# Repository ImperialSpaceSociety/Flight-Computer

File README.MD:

# Imperial College Space Society - High-power Rocketry

## Rocket

The rocket was initially designed in a program called OpenRocket and then the particular components were designed in Fusion 360 and manufactured using 3D printers or a laser cutter.

## Flight computer

The flight computer is based on STM32 platform and the main diagram with its components can be seen below.

The following picture shows the 3D render of the flight computer designed in KiCAD.

## Receiver

The table documents the connection of the radio module into STM32 F446RE Nucleo Board used as a receiver.

| **Lambda 9D pin** | **STM32 Nucleo F446RE pin** |
|-------------------|-----------------------------|
| nSel - 16         |             GND             |
| SDI - 15          |             PA7             |
| SDO - 14          |             PA6             |
| SCLK - 13         |             PA5             |
| RESET - 12        |             PB12            |
| GND - 2           |             GND             |
| Vcc - 3           |             3V3             |
| RX_SWITCH - 4     |             PC2             |
| TX_SWITCH - 5     |             PA4             |

## Launch

The rocket was successfully launched and recovered on 9th July 2023 in Twycross, Leicestershire. The rocket reached the altitude of 721 m after 11.4 s of flight.

## Future improvements

- UART connection for debugging
- Button/jumper pin header for resetting STM32
- Code for IMU, magnetometer and flashchip
- FreeRTOS for the flight computer
- Modify serial logging script such that the incoming data is being processed and then saved as csv

## Repository content

- `Assets` - This folder contains images and plots for the `README.md` file.
- `Hardware/circuit board design v1.0` - First version of the hardware files of the flight computer.
- `Hardware/circuit board design v2.1` - Second version of the hardware files of the flight computer.
- `Hardware/Documentation` - Documentation files with spreadsheets containing components selection and power consumption.
- `Rocket` - This folder contains files simulation and design files for the rocket.
- `References` - This folder contains datasheets and manuals relevant to the components used for the flight computer.
- `Software/Dev board code` - This folder contains projects used to develop and test libraries for each of the components of the computer.
- `Software/revision_1` - First version of the flight computer software.
- `Software/revision_1_rx` - First version of the receiver software.
- `Software/serial_logging` - Code for the serial logging of the received data.

## Team (Academic year 2022/2023)

- Awais Khawaja (Rocket team lead)
- Rohan Kukreti, Stephen Liu (Nose cone)
- Heather Boatin (Recovery system)
- Denzel Goh, Dongxiao Jiang (Fins)
- Jack Crane (Engine mount)
- Timothy Newman, Lou Alsteens, Jakub Jędrzejewski (PCB)
- Václav Pavlíček, Richard Hu, Benny Liu (Software)

## Acknowledgements

We would like to thank Victor Boddy from the Electrical Engineering Undergraduate lab and the Advanced Hackspace staff for their help and support.

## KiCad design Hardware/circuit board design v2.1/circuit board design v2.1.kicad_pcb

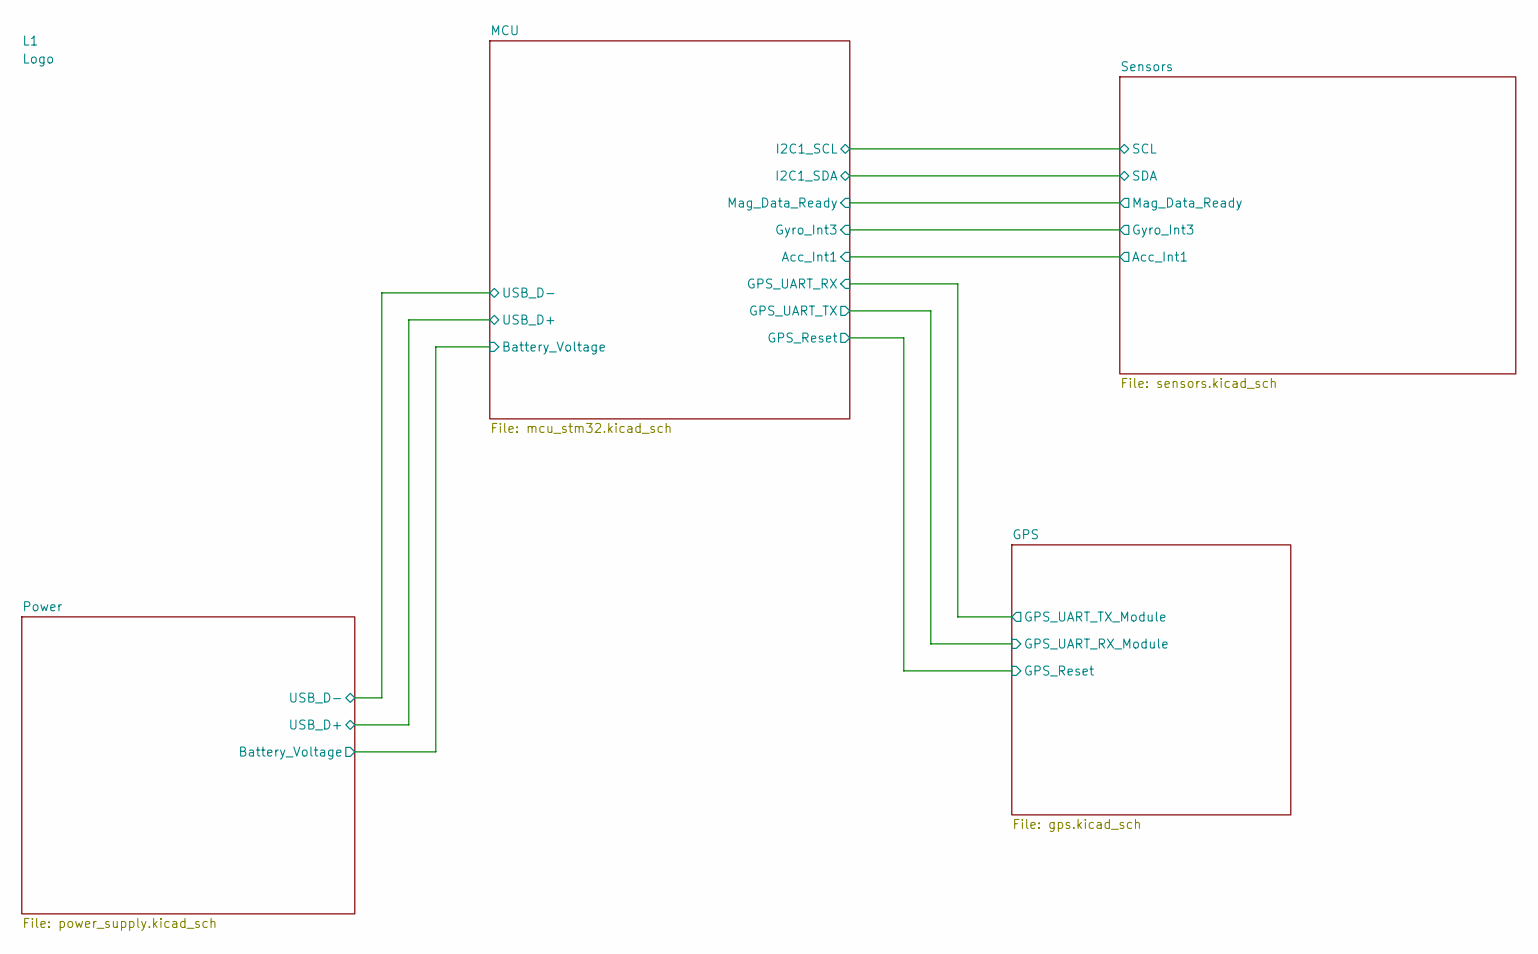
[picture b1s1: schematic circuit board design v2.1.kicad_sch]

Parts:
L1: Logo; ICSS_Logo

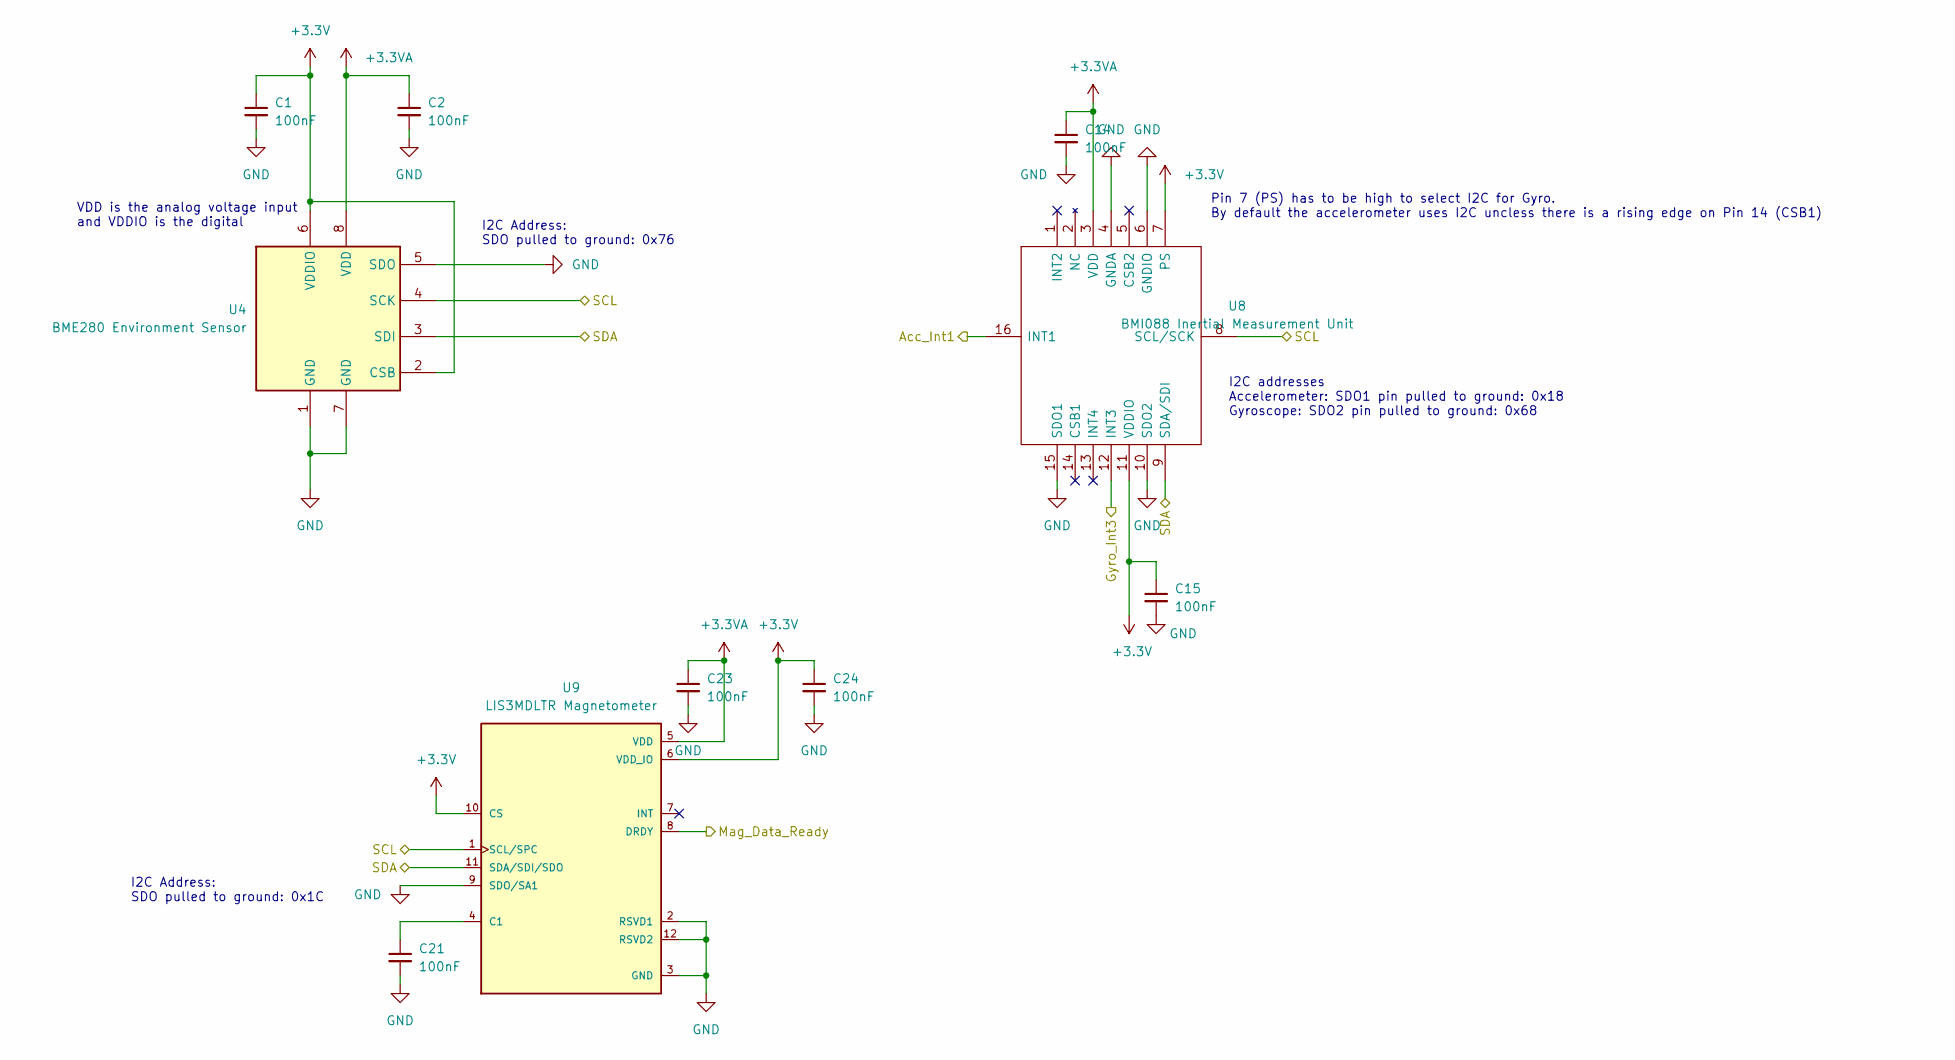
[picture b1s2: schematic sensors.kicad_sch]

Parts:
C1, C2, C14, C15, C21, C23, C24: 100nF; C_0603_1608Metric
U4: BME280 Environment Sensor; Bosch_LGA-8_2.5x2.5mm_P0.65mm_ClockwisePinNumbering
U8: BMI088 Inertial Measurement Unit; BMI088; Manufacturer_Part_Number BMI088; Mouser Part Number 262-BMI088
U9: LIS3MDLTR Magnetometer; XDCR_LIS3MDLTR; PARTREV 6

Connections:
+3.3V: C1.1, C15.1, C24.1, U4.2 (CSB), U4.6 (VDDIO), U8.7 (PS), U8.11 (VDDIO), U9.6 (VDD_IO), U9.10 (CS); also elsewhere on the board
+3.3VA: C2.1, C14.1, C23.1, U4.8 (VDD), U8.3 (VDD), U9.5 (VDD); also elsewhere on the board
/MCU/Acc_Int1: U8.16 (INT1); also elsewhere on the board
/MCU/Gyro_Int3: U8.12 (INT3); also elsewhere on the board
/MCU/I2C1_SCL: U4.4 (SCK), U8.8 (SCL/SCK), U9.1 (SCL/SPC); also elsewhere on the board
/MCU/I2C1_SDA: U4.3 (SDI), U8.9 (SDA/SDI), U9.11 (SDA/SDI/SDO); also elsewhere on the board
/MCU/Mag_Data_Ready: U9.8 (DRDY); also elsewhere on the board
GND: C1.2, C2.2, C14.2, C15.2, C21.2, C23.2, C24.2, U4.1 (GND), U4.5 (SDO), U4.7 (GND), U8.4 (GNDA), U8.6 (GNDIO), U8.10 (SDO2), U8.15 (SDO1), U9.2 (RSVD1), U9.3 (GND), U9.9 (SDO/SA1), U9.12 (RSVD2); also elsewhere on the board
unnamed: C21.1, U9.4 (C1)

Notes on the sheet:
VDD is the analog voltage input and VDDIO is the digital
Pin 7 (PS) has to be high to select I2C for Gyro. By default the accelerometer uses I2C uncless there is a rising edge on Pin 14 (CSB1)
I2C addresses Accelerometer: SDO1 pin pulled to ground: 0x18 Gyroscope: SDO2 pin pulled to ground: 0x68
I2C Address: SDO pulled to ground: 0x1C
I2C Address: SDO pulled to ground: 0x76

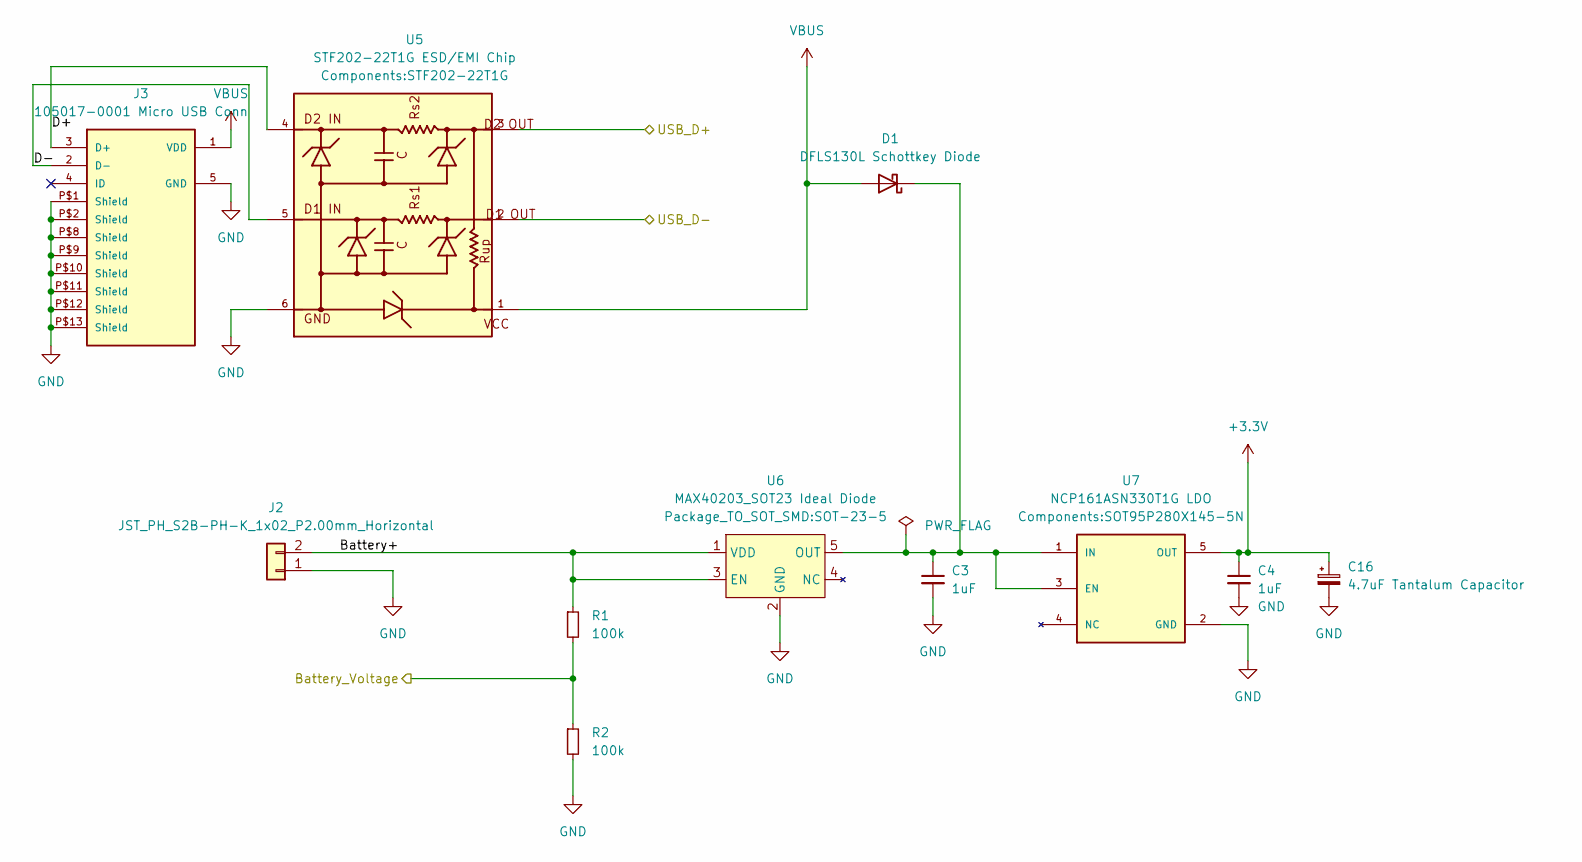
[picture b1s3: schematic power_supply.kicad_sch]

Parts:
C3, C4: 1uF; C_0603_1608Metric
C16: 4.7uF Tantalum Capacitor; C_1206_3216Metric_Pad1.33x1.80mm_HandSolder
D1: DFLS130L Schottkey Diode; PowerDI123
J2: JST_PH_S2B-PH-K_1x02_P2.00mm_Horizontal
J3: 105017-0001 Micro USB Conn; MOLEX_105017-0001
R1, R2: 100k; R_0603_1608Metric
U5: STF202-22T1G ESD/EMI Chip; STF202-22T1G
U6: MAX40203_SOT23 Ideal Diode; SOT-23-5
U7: NCP161ASN330T1G LDO; SOT95P280X145-5N; PARTREV Rev. 18

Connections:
+3.3V: C4.1, C16.1, U7.5 (OUT); also elsewhere on the board
/MCU/Battery_Voltage: R1.2, R2.1; also elsewhere on the board
/MCU/USB_D+: U5.3; also elsewhere on the board
/MCU/USB_D-: U5.2; also elsewhere on the board
/Power/Battery+: J2.2, R1.1, U6.1 (VDD), U6.3 (EN)
/Power/D+: J3.3 (D+), U5.4
/Power/D-: J3.2 (D-), U5.5
GND: C3.2, C4.2, C16.2, J2.1, J3.5 (GND), J3.P$1 (Shield), J3.P$2 (Shield), J3.P$8 (Shield), J3.P$9 (Shield), J3.P$10 (Shield), J3.P$11 (Shield), J3.P$12 (Shield), J3.P$13 (Shield), R2.2, U5.6, U6.2 (GND), U7.2 (GND); also elsewhere on the board
unnamed: C3.1, D1.1 (K), U6.5 (OUT), U7.1 (IN), U7.3 (EN)
VBUS: D1.2 (A), J3.1 (VDD), U5.1

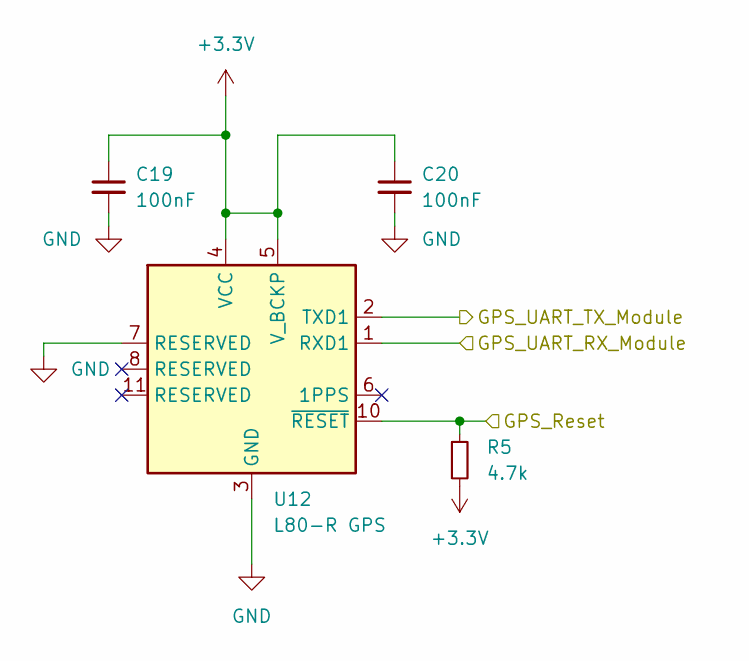
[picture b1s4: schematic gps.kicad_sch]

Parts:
C19, C20: 100nF; C_0603_1608Metric
R5: 4.7k; R_0603_1608Metric
U12: L80-R GPS; Quectel_L80-R

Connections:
+3.3V: C19.1, C20.1, R5.2, U12.4 (VCC), U12.5 (V_BCKP); also elsewhere on the board
/GPS/GPS_Reset: R5.1, U12.10 (~RESET); also elsewhere on the board
/GPS/GPS_UART_RX_Module: U12.1 (RXD1); also elsewhere on the board
/GPS/GPS_UART_TX_Module: U12.2 (TXD1); also elsewhere on the board
GND: C19.2, C20.2, U12.3 (GND), U12.7 (RESERVED), U12.12 (GND); also elsewhere on the board

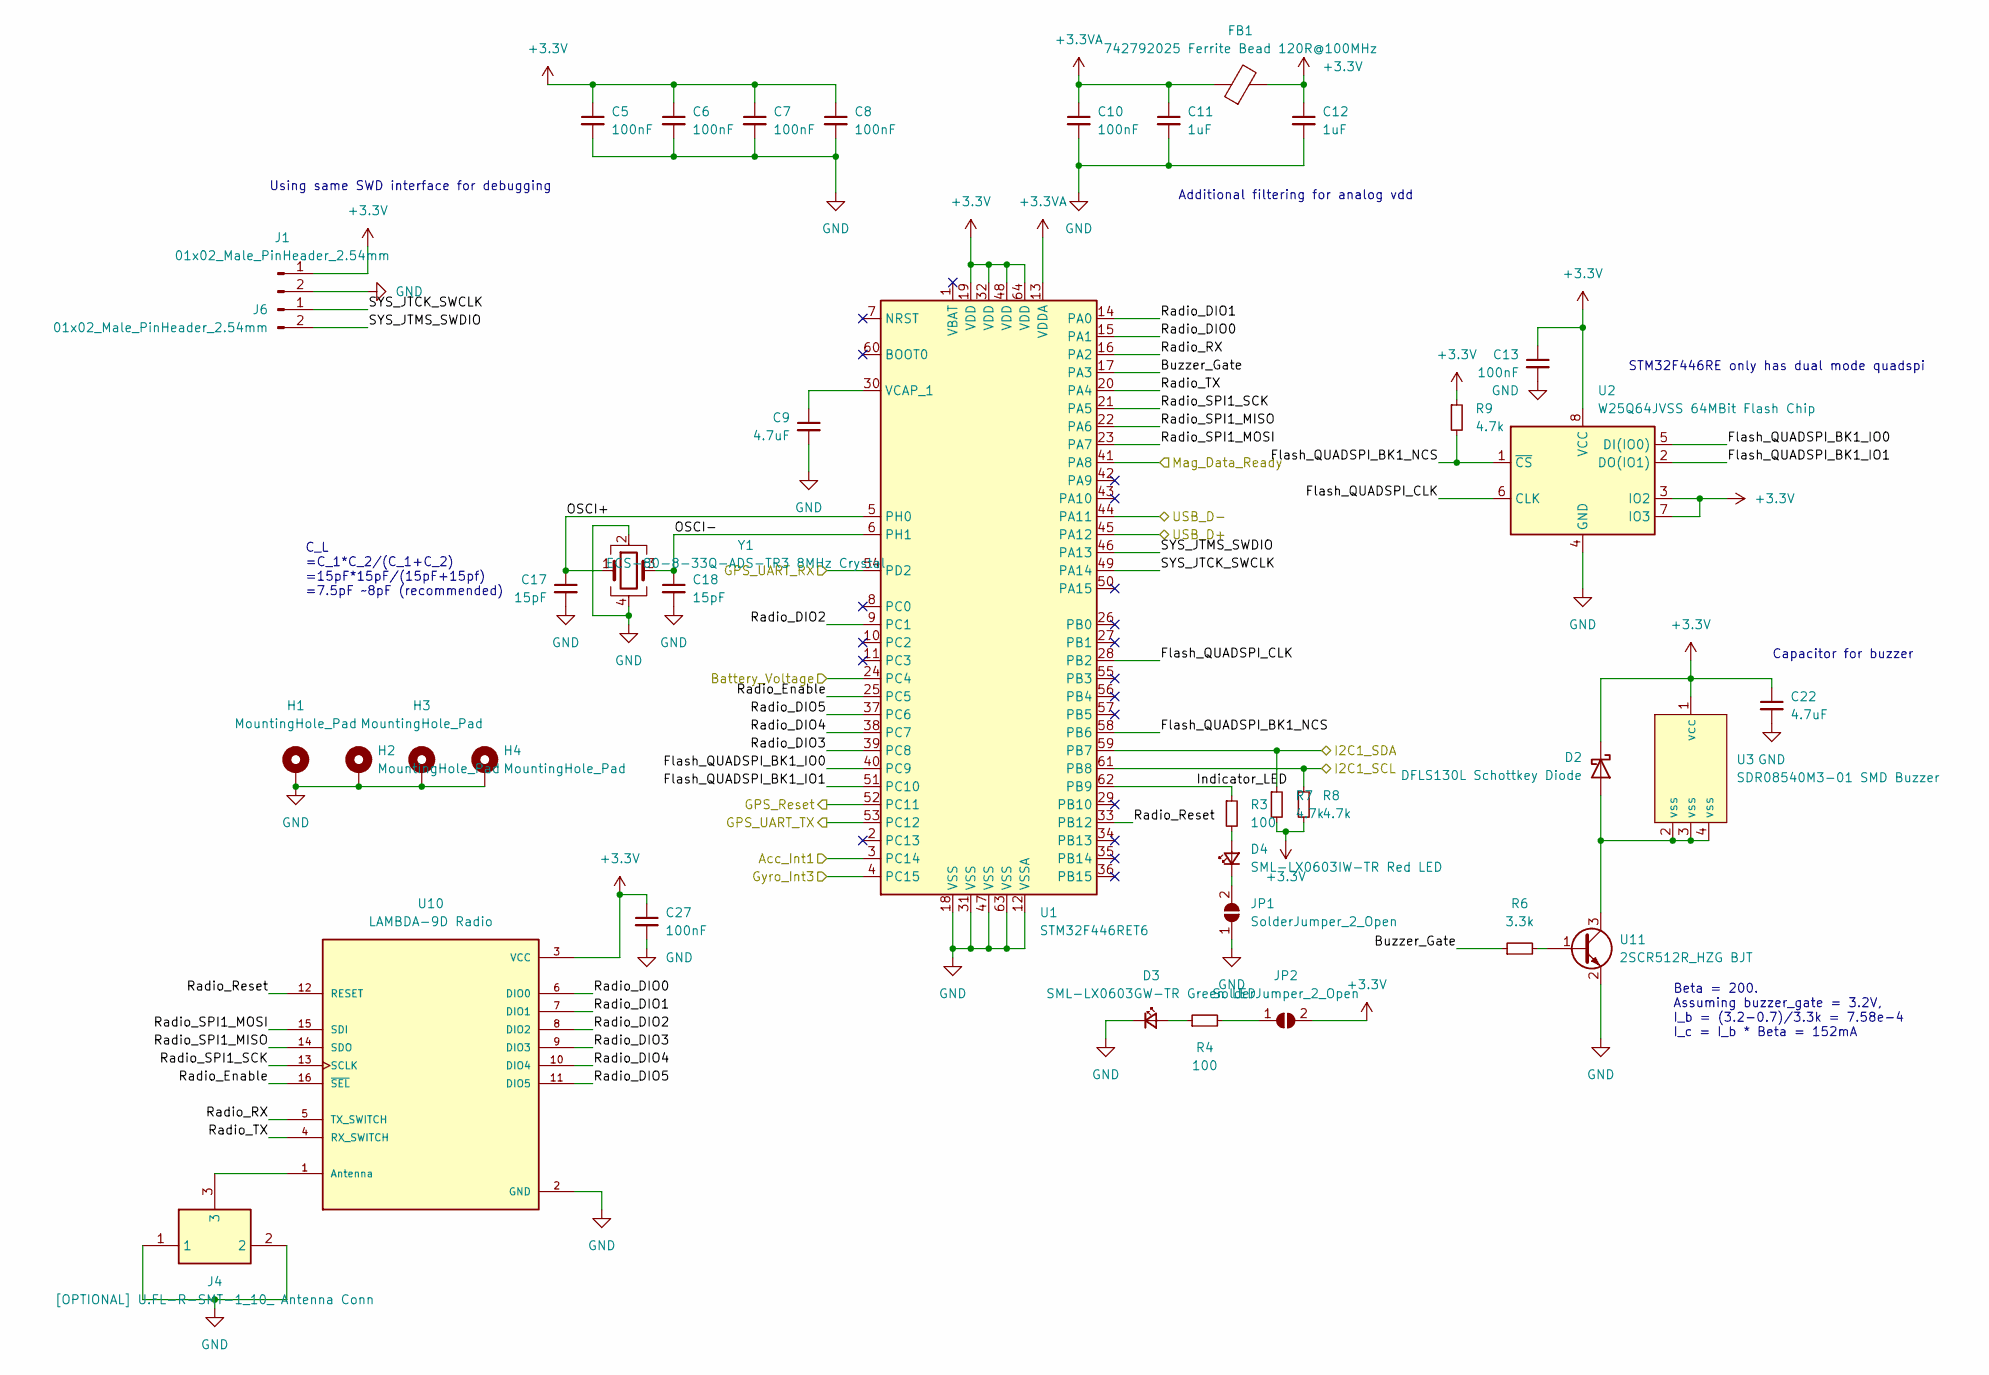
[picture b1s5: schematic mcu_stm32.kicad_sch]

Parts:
C5, C6, C7, C8, C10, C13: 100nF; C_0603_1608Metric
C9, C22: 4.7uF; C_0603_1608Metric
C11, C12: 1uF; C_0603_1608Metric
C17, C18: 15pF; C_0603_1608Metric
C27: 100nF; C_0603_1608Metric_Pad1.08x0.95mm_HandSolder
D2: DFLS130L Schottkey Diode; PowerDI123
D3: SML-LX0603GW-TR Green LED; C_0603_1608Metric
D4: SML-LX0603IW-TR Red LED; C_0603_1608Metric
FB1: 742792025 Ferrite Bead 120R@100MHz; R_0805_2012Metric_Pad1.20x1.40mm_HandSolder
H1, H2, H3, H4: MountingHole_Pad; MountingHole_3.2mm_M3_ISO7380_Pad_TopBottom
J1, J6: 01x02_Male_PinHeader_2.54mm; PinHeader_1x02_P2.54mm_Vertical
J4: [OPTIONAL] U.FL-R-SMT-1_10_ Antenna Conn; U.FL-R-SMT-1_10_; Manufacturer_Part_Number U.FL-R-SMT-1(10); Mouser Part Number 798-U.FL-R-SMT-110
JP1, JP2: SolderJumper_2_Open; SolderJumper-2_P1.3mm_Open_TrianglePad1.0x1.5mm
R3, R4: 100; R_0603_1608Metric
R6: 3.3k; R_0603_1608Metric
R7, R8, R9: 4.7k; R_0603_1608Metric
U1: STM32F446RET6; LQFP-64_10x10mm_P0.5mm
U2: W25Q64JVSS 64MBit Flash Chip; W25Q64JVSSIQ
U3: SDR08540M3-01 SMD Buzzer; SDR08540M3-01 Buzzer
U10: LAMBDA-9D Radio; XCVR_LAMBDA-9D; PARTREV N/A
U11: 2SCR512R_HZG BJT; 2SCR512RHZG
Y1: ECS-80-8-33Q-ADS-TR3 8MHz Crystal; ECS-80-8-33Q-ADS-TR3 Crystal

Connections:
+3.3V: C5.1, C6.1, C7.1, C8.1, C12.1, C13.1, C22.1, C27.1, D2.1 (K), FB1.2, J1.1, JP2.2 (B), R7.2, R8.2, R9.1, U1.19 (VDD), U1.32 (VDD), U1.48 (VDD), U1.64 (VDD), U2.3 (IO2), U2.7 (IO3), U2.8 (VCC), U3.1 (vcc), U10.3 (VCC); also elsewhere on the board
+3.3VA: C10.1, C11.1, FB1.1, U1.13 (VDDA); also elsewhere on the board
/GPS/GPS_Reset: U1.52 (PC11); also elsewhere on the board
/GPS/GPS_UART_RX_Module: U1.53 (PC12); also elsewhere on the board
/GPS/GPS_UART_TX_Module: U1.54 (PD2); also elsewhere on the board
/MCU/Acc_Int1: U1.3 (PC14); also elsewhere on the board
/MCU/Battery_Voltage: U1.24 (PC4); also elsewhere on the board
/MCU/Buzzer_Gate: R6.1, U1.17 (PA3)
/MCU/Flash_QUADSPI_BK1_IO0: U1.40 (PC9), U2.5 (DI(IO0))
/MCU/Flash_QUADSPI_BK1_IO1: U1.51 (PC10), U2.2 (DO(IO1))
/MCU/Flash_QUADSPI_BK1_NCS: R9.2, U1.58 (PB6), U2.1 (~CS)
/MCU/Flash_QUADSPI_CLK: U1.28 (PB2), U2.6 (CLK)
/MCU/Gyro_Int3: U1.4 (PC15); also elsewhere on the board
/MCU/I2C1_SCL: R8.1, U1.61 (PB8); also elsewhere on the board
/MCU/I2C1_SDA: R7.1, U1.59 (PB7); also elsewhere on the board
/MCU/Indicator_LED: R3.1, U1.62 (PB9)
/MCU/Mag_Data_Ready: U1.41 (PA8); also elsewhere on the board
/MCU/OSCI+: C17.1, U1.5 (PH0), Y1.1
/MCU/OSCI-: C18.1, U1.6 (PH1), Y1.3
/MCU/Radio_DIO0: U1.15 (PA1), U10.6 (DIO0)
/MCU/Radio_DIO1: U1.14 (PA0), U10.7 (DIO1)
/MCU/Radio_DIO2: U1.9 (PC1), U10.8 (DIO2)
/MCU/Radio_DIO3: U1.39 (PC8), U10.9 (DIO3)
/MCU/Radio_DIO4: U1.38 (PC7), U10.10 (DIO4)
/MCU/Radio_DIO5: U1.37 (PC6), U10.11 (DIO5)
/MCU/Radio_Enable: U1.25 (PC5), U10.16 (~SEL)
/MCU/Radio_RX: U1.16 (PA2), U10.5 (TX_SWITCH)
/MCU/Radio_Reset: U1.33 (PB12), U10.12 (RESET)
/MCU/Radio_SPI1_MISO: U1.22 (PA6), U10.14 (SDO)
/MCU/Radio_SPI1_MOSI: U1.23 (PA7), U10.15 (SDI)
/MCU/Radio_SPI1_SCK: U1.21 (PA5), U10.13 (SCLK)
/MCU/Radio_TX: U1.20 (PA4), U10.4 (RX_SWITCH)
/MCU/SYS_JTCK_SWCLK: J6.1, U1.49 (PA14)
/MCU/SYS_JTMS_SWDIO: J6.2, U1.46 (PA13)
/MCU/USB_D+: U1.45 (PA12); also elsewhere on the board
/MCU/USB_D-: U1.44 (PA11); also elsewhere on the board
GND: C5.2, C6.2, C7.2, C8.2, C9.2, C10.2, C11.2, C12.2, C13.2, C17.2, C18.2, C22.2, C27.2, D3.1 (K), H1.1, H2.1, H3.1, H4.1, J1.2, J4.1, J4.2, JP1.1 (A), U1.12 (VSSA), U1.18 (VSS), U1.31 (VSS), U1.47 (VSS), U1.63 (VSS), U2.4 (GND), U10.2 (GND), U11.2 (E), Y1.2, Y1.4; also elsewhere on the board
unnamed: C9.1, U1.30 (VCAP_1)
unnamed: D2.2 (A), U3.2 (vss), U3.3 (vss), U3.4 (vss), U11.3 (C)
unnamed: D3.2 (A), R4.1
unnamed: D4.1 (K), JP1.2 (B)
unnamed: D4.2 (A), R3.2
unnamed: J4.3, U10.1 (Antenna)
unnamed: JP2.1 (A), R4.2
unnamed: R6.2, U11.1 (B)

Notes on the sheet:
Capacitor for buzzer
Using same SWD interface for debugging
STM32F446RE only has dual mode quadspi
Additional filtering for analog vdd
C_L =C_1*C_2/(C_1+C_2) =15pF*15pF/(15pF+15pf) =7.5pF ~8pF (recommended)
Beta = 200. Assuming buzzer_gate = 3.2V, I_b = (3.2-0.7)/3.3k = 7.58e-4 I_c = I_b * Beta = 152mA

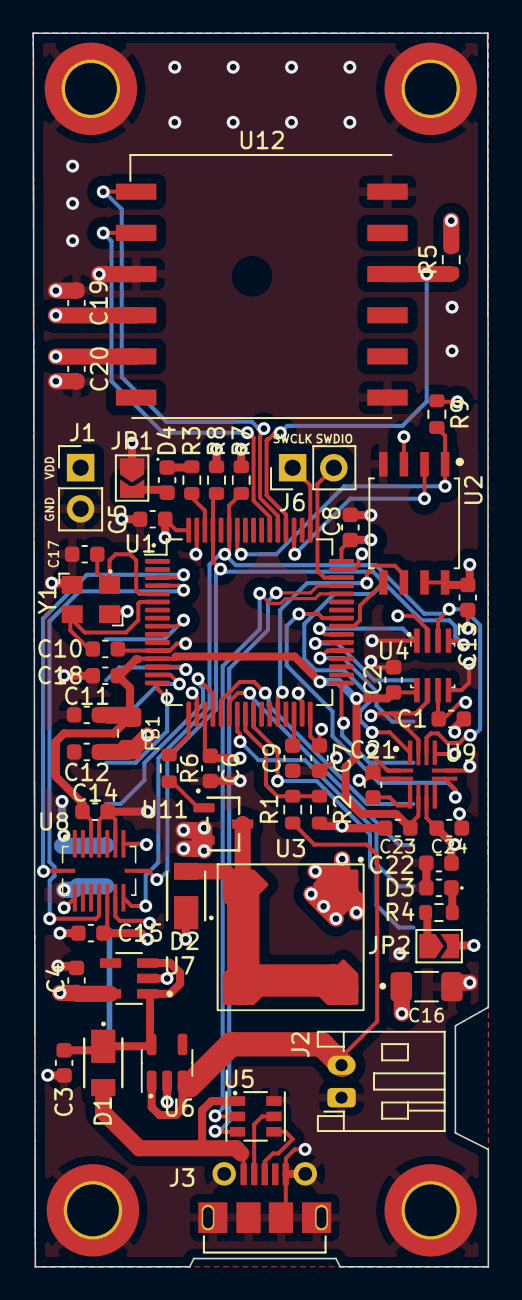
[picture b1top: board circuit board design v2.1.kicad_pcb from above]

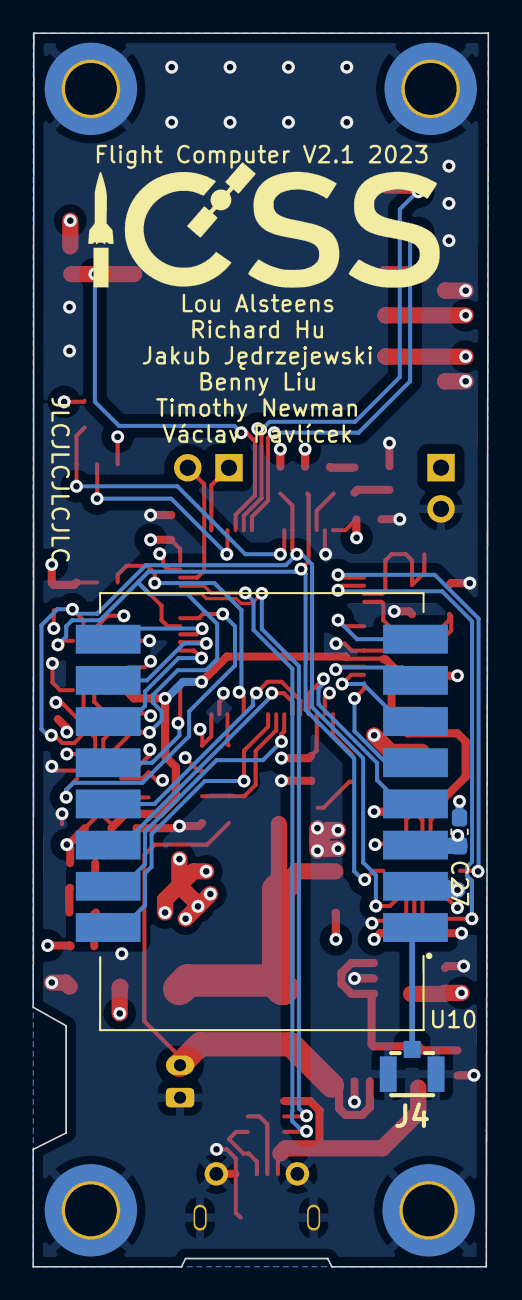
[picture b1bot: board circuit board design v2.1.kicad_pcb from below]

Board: 4 copper layers, 28.1 x 76.1 mm, 64 parts (4 on the bottom side), 51 nets.

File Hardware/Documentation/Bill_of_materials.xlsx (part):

Source: | C:\Users\timot\Documents\Programming\SpaceSoc\Flight-Computer\Hardware\circuit 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
Date: | 45080.649074074077
Tool: | Eeschema (6.0.8)
Generator: | C:\Program Files\KiCad\6.0\bin\scripting\plugins/bom_csv_grouped_by_value.py
Component Count: | 56
Individual Components:
Item | Qty | Reference(s) | Value | LibPart | Footprint | Datasheet | AVAILABILITY | Arrow Part Number | Arrow Price/Stock | DESCRIPTION | Datasheet_1 | Description | Footprint_1 | Height | MANUFACTURER | MAXIMUM_PACKAGE_HEIGHT | MF | MP | Manufacturer_Name | Manufacturer_Part_Number | Mouser Part Number | Mouser Price/Stock | PACKAGE | PARTREV | PRICE | Reference_1 | SNAPEDA_PACKAGE_ID | SNAPEDA_PN | STANDARD | Value_1
 |  | C1 | 100nF | Components:C_0603 | Components:C_0603_1608Metric | ~
 |  | C2 | 100nF | Components:C_0603 | Components:C_0603_1608Metric | ~
 |  | C3 | 1uF | Components:C_0603 | Components:C_0603_1608Metric | ~
 |  | C4 | 1uF | Components:C_0603 | Components:C_0603_1608Metric | ~
 |  | C5 | 100nF | Components:C_0603 | Components:C_0603_1608Metric | ~
 |  | C6 | 100nF | Components:C_0603 | Components:C_0603_1608Metric | ~
 |  | C7 | 100nF | Components:C_0603 | Components:C_0603_1608Metric | ~
 |  | C8 | 100nF | Components:C_0603 | Components:C_0603_1608Metric | ~
 |  | C9 | 4.7uF | Components:C_0603 | Components:C_0603_1608Metric | ~
 |  | C10 | 100nF | Components:C_0603 | Components:C_0603_1608Metric | ~
 |  | C11 | 1uF | Components:C_0603 | Components:C_0603_1608Metric | ~
 |  | C12 | 1uF | Components:C_0603 | Components:C_0603_1608Metric | ~
 |  | C13 | 100nF | Components:C_0603 | Components:C_0603_1608Metric | ~
 |  | C14 | 100nF | Components:C_0603 | Components:C_0603_1608Metric | ~
 |  | C15 | 100nF | Components:C_0603 | Components:C_0603_1608Metric | ~
 |  | C16 | 4.7uF Tantalum Capacitor | Device:C_Polarized_Small | Capacitor_SMD:C_1206_3216Metric_Pad1.33x1.80mm_HandSolder | ~
 |  | C17 | 15pF | Components:C_0603 | Components:C_0603_1608Metric | ~
 |  | C18 | 15pF | Components:C_0603 | Components:C_0603_1608Metric | ~
 |  | C19 | 100nF | Components:C_0603 | Components:C_0603_1608Metric | ~
 |  | C20 | 100nF | Components:C_0603 | Components:C_0603_1608Metric | ~
 |  | C21 | 100nF | Components:C_0603 | Components:C_0603_1608Metric | ~
 |  | C22 | 4.7uF | Components:C_0603 | Components:C_0603_1608Metric | ~
 |  | C23 | 100nF | Components:C_0603 | Components:C_0603_1608Metric | ~
 |  | C24 | 100nF | Components:C_0603 | Components:C_0603_1608Metric | ~
 |  | C27 | 100nF | Device:C_Small | Capacitor_SMD:C_0603_1608Metric_Pad1.08x0.95mm_HandSolder | ~
 |  | D1 | DFLS130L Schottkey Diode | Components:DFLS130L | Components:PowerDI123 | ~
 |  | D2 | DFLS130L Schottkey Diode | Components:DFLS130L | Components:PowerDI123 | ~
 |  | D3 | SML-LX0603GW-TR Green LED | Components:LED_0603 | Components:C_0603_1608Metric | ~
 |  | D4 | SML-LX0603IW-TR Red LED | Components:LED_0603 | Components:C_0603_1608Metric | ~
 |  | FB1 | 742792025 Ferrite Bead 120R@100MHz | Device:FerriteBead | Resistor_SMD:R_0805_2012Metric_Pad1.20x1.40mm_HandSolder | ~
 |  | J1 | 01x02_Male_PinHeader_2.54mm | Connector:Conn_01x02_Male | Connector_PinHeader_2.54mm:PinHeader_1x02_P2.54mm_Vertical | ~
 |  | J2 | JST_PH_S2B-PH-K_1x02_P2.00mm_Horizontal | Connector_Generic:Conn_01x02 | Components:JST_PH_S2B-PH-K_1x02_P2.00mm_Horizontal | ~
 |  | J3 | 105017-0001 Micro USB Conn | Components:105017-0001 | MOLEX_105017-0001 | https://www.mouser.co.uk/datasheet/2/276/1/1050170001_IO_CON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
 |  | J4 | [OPTIONAL] U.FL-R-SMT-1_10_ Antenna Conn | Components:U.FL-R-SMT-1_10_ | Components:U.FL-R-SMT-1_10_ | https://www.hirose.com/product/document?clcode=CL0331-0472-2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 |  | U.FL-R-SMT-1(10) | https://www.arrow.com/en/products/u.fl-r-smt-1-10/hirose-electric |  | https://www.hirose.com/product/document?clcode=CL0331-0472-2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 |  | U.FL-R-SMT-1(10) |  |  |  |  |  | Hirose | U.FL-R-SMT-1(10) | 798-U.FL-R-SMT-110 | https://www.mouser.co.uk/ProductDetail/Hirose-Connector/U.FL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 |  |  |  | J |  |  |  | U.FL-R-SMT-1_10_
 |  | J6 | 01x02_Male_PinHeader_2.54mm | Connector:Conn_01x02_Male | Connector_PinHeader_2.54mm:PinHeader_1x02_P2.54mm_Vertical | ~
 |  | R1 | 100k | Components:R_0603 | Components:R_0603_1608Metric | ~
 |  | R2 | 100k | Components:R_0603 | Components:R_0603_1608Metric | ~
 |  | R3 | 100 | Components:R_0603 | Components:R_0603_1608Metric | ~
 |  | R4 | 100 | Components:R_0603 | Components:R_0603_1608Metric | ~
 |  | R5 | 4.7k | Components:R_0603 | Components:R_0603_1608Metric | ~
 |  | R6 | 3.3k | Components:R_0603 | Components:R_0603_1608Metric | ~
 |  | R7 | 4.7k | Components:R_0603 | Components:R_0603_1608Metric | ~
 |  | R8 | 4.7k | Components:R_0603 | Components:R_0603_1608Metric | ~
 |  | U1 | STM32F446RETx | MCU_ST_STM32F4:STM32F446RETx | Components:LQFP-64_10x10mm_P0.5mm | http://www.st.com/st-web-ui/static/active/en/resource/techni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
 |  | U2 | W25Q64JVSS 64MBit Flash Chip | Components:W25Q64JVSS | Components:W25Q64JVSSIQ | https://www.winbond.com/resource-files/W25Q64JV%20RevK%20031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
 |  | U3 | SDR08540M3-01 SMD Buzzer | Components:SDR08540M3-01 | Components:SDR08540M3-01 Buzzer | https://docs.rs-online.com/16ce/0900766b815934ae.pdf
 |  | U4 | BME280 Environment Sensor | Sensor:BME280 | Package_LGA:Bosch_LGA-8_2.5x2.5mm_P0.65mm_ClockwisePinNumbering | https://ae-bst.resource.bosch.com/media/_tech/media/datashee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
 |  | U5 | STF202-22T1G ESD/EMI Chip | Components:STF202-22T1G | Components:STF202-22T1G
 |  | U6 | MAX40203_SOT23 Ideal Diode | Components:MAX40203_SOT23 | Package_TO_SOT_SMD:SOT-23-5
 |  | U7 | NCP161ASN330T1G LDO | Components:NCP161ASN180T1G | Components:SOT95P280X145-5N | https://www.mouser.co.uk/datasheet/2/308/1/NCP161_D-2316989.pdf |  |  |  |  |  |  |  |  | Onsemi | 1.45 mm |  |  |  |  |  |  |  | Rev. 18 |  |  |  | NCP161ASN180T1G | IPC-7351B
 |  | U8 | BMI088 Inertial Measurement Unit | Components:BMI088 | Components:BMI088 | https://datasheet.datasheetarchive.com/originals/distributor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 |  | BMI088 | https://www.arrow.com/en/products/bmi088/bosch?region=europe |  |  | Inertial Measurement Unit Digital Output 2.5V/3.3V Automotive |  | 1.45 |  |  |  |  | BOSCH | BMI088 | 262-BMI088 | https://www.mouser.co.uk/ProductDetail/Bosch-Sensortec/BMI08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
 |  | U9 | LIS3MDLTR Magnetometer | Components:LIS3MDLTR | Components:XDCR_LIS3MDLTR |  | Unavailable |  |  | LIS3MDL Series 3 Axis Â±2/Â±8/Â±12/Â±16 g 3.6V High Performance Magnetometer LG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 |  |  |  |  |  | 1mm | STMicroelectronics | LIS3MDLTR |  |  |  |  | VFLGA-12 STMicroelectronics | 6 | None |  |  |  | Manufacturer Recommendation
 |  | U10 | LAMBDA-9D Radio | Components:LAMBDA-9D | Components:XCVR_LAMBDA-9D |  |  |  |  |  |  |  |  |  | RF Solutions | 5.81 mm |  |  |  |  |  |  |  | N/A |  |  | 63698 | LAMBDA-9D | Manufacturer Recommendations
 |  | U11 | 2SCR512R_HZG BJT | Components:2SCR512R_HZG | Components:2SCR512RHZG | https://fscdn.rohm.com/en/products/databook/datasheet/discre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
 |  | U12 | L80-R GPS | Components:L80-R | Components:Quectel_L80-R | https://www.quectel.com/UploadImage/Downlad/Quectel_L80-R_Ha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
 |  | Y1 | ECS-80-8-33Q-ADS-TR3 8MHz Crystal | Device:Crystal_GND24 | Components:ECS-80-8-33Q-ADS-TR3 Crystal | ~
Collated Components:
Item | Qty | Reference(s) | Value |  |  |  |  |  |  |  |  |  |  |  |  |  |  |  |  |  |  |  |  |  |  |  |  |  | STANDARD | Value_1
1 | 15 | C1, C2, C5, C6, C7, C8, C10, C13, C14, C15, C19, C20, C21, C23, C24 | 100nF
2 | 4 | C3, C4, C11, C12 | 1uF
3 | 2 | C9, C22 | 4.7uF
4 | 1 | C16 | 4.7uF Tantalum Capacitor
5 | 2 | C17, C18 | 15pF
6 | 1 | C27 | 100nF
7 | 2 | D1, D2 | DFLS130L Schottkey Diode
8 | 1 | D3 | SML-LX0603GW-TR Green LED
9 | 1 | D4 | SML-LX0603IW-TR Red LED
10 | 1 | FB1 | 742792025 Ferrite Bead 120R@100MHz
11 | 2 | J1, J6 | 01x02_Male_PinHeader_2.54mm
12 | 1 | J2 | JST_PH_S2B-PH-K_1x02_P2.00mm_Horizontal
13 | 1 | J3 | 105017-0001 Micro USB Conn
14 | 1 | J4 | [OPTIONAL] U.FL-R-SMT-1_10_ Antenna Conn
15 | 2 | R1, R2 | 100k
16 | 2 | R3, R4 | 100
17 | 3 | R5, R7, R8 | 4.7k
18 | 1 | R6 | 3.3k
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
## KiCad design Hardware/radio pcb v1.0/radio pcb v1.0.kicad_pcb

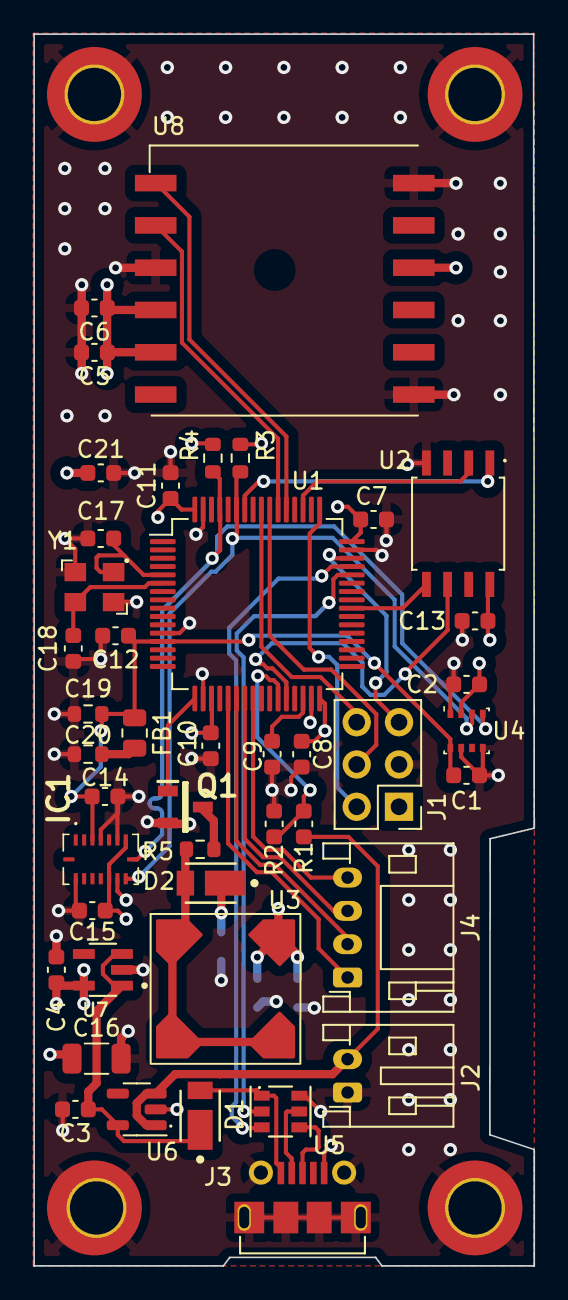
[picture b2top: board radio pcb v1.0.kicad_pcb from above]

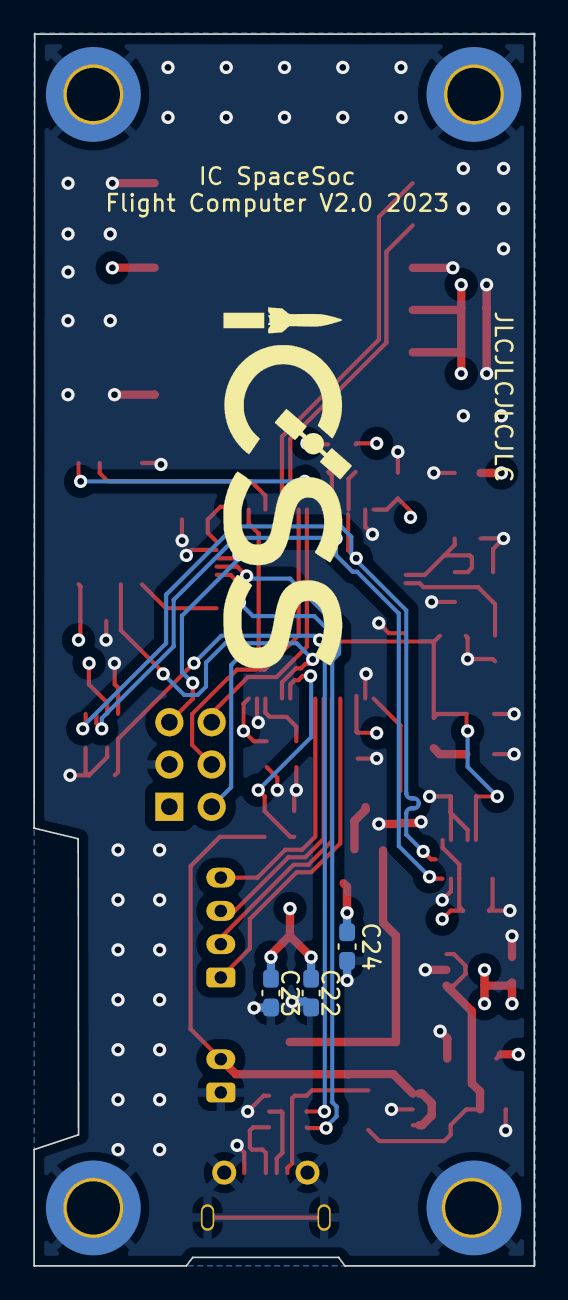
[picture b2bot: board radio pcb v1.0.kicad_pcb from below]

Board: 4 copper layers, 30.0 x 74.0 mm, 51 parts (3 on the bottom side), 34 nets.

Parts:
C1, C2, C5, C6, C7, C8, C10, C11, C12, C13, C14, C15: 100nF; C_0603_1608Metric
C3, C4: 1uF; C_0603_1608Metric
C9: 4.7u; C_0603_1608Metric
C16: 1uF; C_1206_3216Metric
C17, C18: 8pF; C_0603_1608Metric
C19, C20: 1uF; R_0603_1608Metric
C21: 4.7uF; C_0603_1608Metric
C22, C23, C24: 1uF; C_0603_1608Metric_Pad1.08x0.95mm_HandSolder
D1, D2: DFLS130L; PowerDI123
FB1: 120R@100MHz; R_0805_2012Metric
H1, H2, H3, H4: MountingHole_Pad; MountingHole_3.2mm_M3_ISO7380_Pad_TopBottom
IC1: BMI088
J1: Conn_01x06_Male; PinHeader_2x03_P2.54mm_Vertical
J2: Conn_01x02; JST_PH_S2B-PH-K_1x02_P2.00mm_Horizontal
J3: 105017-0001; MOLEX_105017-0001
J4: Conn_01x04; JST_PH_S4B-PH-K_1x04_P2.00mm_Horizontal
Q1: 2N7002-7-F; SOT96P240X120-3N
R1, R2: 100k; C_0603_1608Metric
R3, R4: 4.7k; R_0603_1608Metric
R5: 68; R_0603_1608Metric
U1: STM32F446RETx; LQFP-64_10x10mm_P0.5mm
U2: W25Q64JVSS; W25Q64JVSSIQ
U3: SDR08540M3-01; SDR08540M3-01 Buzzer
U4: BME280; Bosch_LGA-8_2.5x2.5mm_P0.65mm_ClockwisePinNumbering
U5: STF202-22T1G
U6: MAX40203_SOT23; SOT-23-5
U7: NCP161ASN330T1G; SOT95P280X145-5N
U8: L80-M39; Quectel_L80-R
Y1: Crystal_GND24; ECS-80-8-33Q-ADS-TR3 Crystal

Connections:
+3.3V: C2.1, C4.1, C5.1, C6.1, C7.1, C8.1, C10.1, C11.1, C13.1, C15.2, C16.1, C21.1, C22.1, C23.1, C24.1, D2.1 (K), IC1.7 (PS), IC1.11 (VDDIO), J1.1, R3.2, R4.2, U1.19 (VDD), U1.32 (VDD), U1.48 (VDD), U1.64 (VDD), U2.8 (VCC), U3.1 (vcc), U4.2 (CSB), U7.5 (OUT), U8.4 (VCC), U8.5 (V_BCKP), U8.10 (~RESET)
+3.3VA: C1.1, C12.1, C14.1, C19.1, FB1.1, IC1.3 (VDD), U1.13 (VDDA), U4.8 (VDD)
/GPS/rx_gps: U1.53 (PC12), U8.1 (RXD1)
/GPS/tx_gps: U1.54 (PD2), U8.2 (TXD1)
/MCU/PWR_BVOLTS: R1.2, R2.1, U1.27 (PB1)
/MCU/QUADSPI_CLK: U1.28 (PB2), U2.6 (CLK)
/MCU/QUADSPI_IO0: U1.40 (PC9), U2.5 (DI(IO0))
/MCU/QUADSPI_IO1: U1.51 (PC10), U2.2 (DO(IO1))
/MCU/QUADSPI_NCS: U1.58 (PB6), U2.1 (~CS)
/MCU/Radio_Enable: J4.4, U1.24 (PC4)
/MCU/SCL: IC1.8 (SCL/SCK), R4.1, U1.61 (PB8), U4.4 (SCK)
/MCU/SDA: IC1.9 (SDA/SDI), R3.1, U1.59 (PB7), U4.3 (SDI)
/MCU/SPI1_MISO: J4.2, U1.22 (PA6)
/MCU/SPI1_MOSI: J4.3, U1.23 (PA7)
/MCU/SPI1_SCK: J4.1, U1.21 (PA5)
/MCU/SYS_JTCK_SWCLK: J1.2, U1.49 (PA14)
/MCU/SYS_JTDO_SWO: J1.6, U1.56 (PB4)
/MCU/SYS_JTMS_SWDIO: J1.5, U1.46 (PA13)
/MCU/SYS_JTRST: J1.4, U1.55 (PB3)
/MCU/buzzer_gate: Q1.1, U1.17 (PA3)
/MCU/usb_dm: U1.44 (PA11), U5.2
/MCU/usb_dp: U1.45 (PA12), U5.3
GND: C1.2, C2.2, C3.2, C4.2, C5.2, C6.2, C7.2, C8.2, C9.2, C10.2, C11.2, C12.2, C13.2, C14.2, C15.1, C16.2, C17.2, C18.2, C19.2, C20.2, C21.2, C22.2, C23.2, C24.2, H1.1, H2.1, H3.1, H4.1, IC1.4 (GNDA), IC1.6 (GNDIO), IC1.10 (SDO2), IC1.15 (SDO1), J1.3, J2.1, J3.5 (GND), J3.P$1 (Shield), J3.P$2 (Shield), J3.P$8 (Shield), J3.P$9 (Shield), J3.P$10 (Shield), J3.P$11 (Shield), J3.P$12 (Shield), J3.P$13 (Shield), Q1.2, R2.2, U1.12 (VSSA), U1.18 (VSS), U1.31 (VSS), U1.47 (VSS), U1.63 (VSS), U2.4 (GND), U4.1 (GND), U4.5 (SDO), U4.7 (GND), U5.6, U6.2 (GND), U7.2 (GND), U8.3 (GND), U8.7 (RESERVED), U8.12 (GND), Y1.2, Y1.4
unnamed: C3.1, D1.1 (K), U6.5 (OUT), U7.1 (IN), U7.3 (EN)
unnamed: C9.1, U1.30 (VCAP_1)
unnamed: C17.1, U1.5 (PH0), Y1.1
unnamed: C18.1, U1.6 (PH1), Y1.3
unnamed: C20.1, FB1.2
unnamed: J2.2, R1.1, U6.1 (VDD), U6.3 (EN)
unnamed: J3.2 (D-), U5.5
unnamed: J3.3 (D+), U5.4
unnamed: Q1.3, R5.2
unnamed: D2.2 (A), R5.1, U3.2 (vss), U3.3 (vss), U3.4 (vss)
VBUS: D1.2 (A), J3.1 (VDD), U5.1

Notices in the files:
parts and their libraries:
Copyright 2021 Accelerated Designs. All rights reserved.
